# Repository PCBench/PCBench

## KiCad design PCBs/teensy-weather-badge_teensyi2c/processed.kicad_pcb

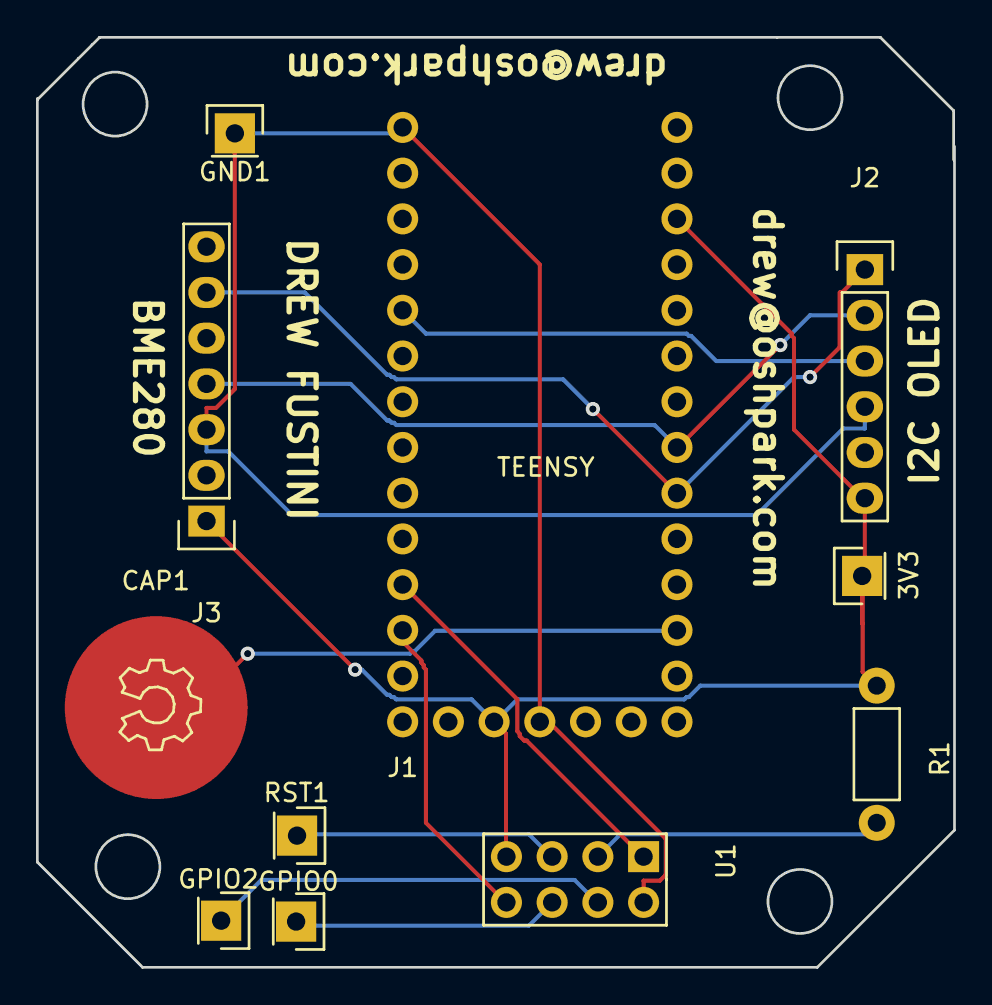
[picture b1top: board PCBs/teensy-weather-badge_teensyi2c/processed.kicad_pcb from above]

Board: 2 copper layers, 51.0 x 51.7 mm, 11 parts (0 on the bottom side), 12 nets.

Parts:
3V3: 3V3; Pin_Header_Straight_1x01
CAP1: CAPSENSE_CIRCLE; CAPSENSE_CIRCLE_D10
GND1: GND; Pin_Header_Straight_1x01
GPIO0: GPIO0; Pin_Header_Straight_1x01
GPIO2: GPIO2; Pin_Header_Straight_1x01
J1: TEENSY3.2-72MHz; TEENSY-LC
J2: OLED-I2C; Pin_Header_Straight_1x06
J3: ADAFRUIT_BME280; Pin_Header_Straight_1x07
R1: R; Resistor_Horizontal_RM7mm
RST1: RST; Pin_Header_Straight_1x01
U1: ESP-01v090; ESP-01

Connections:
/GND: GND1.1, J1.G1, J1.G2, J2.4, J3.3, U1.2
/RST: J1.3, J2.3
/SCK: J1.19, J2.2, J3.4
/SDA: J1.18, J2.1, J3.6
/VIN: 3V3.1, J1.3V1, J1.3V2, J2.6, J3.1, R1.1, U1.7
unnamed: CAP1.1, J1.15
unnamed: GPIO0.1, U1.6
unnamed: GPIO2.1, U1.4
unnamed: J1.9, U1.1
unnamed: J1.10, U1.8
unnamed: R1.2, U1.3
unnamed: RST1.1, U1.5

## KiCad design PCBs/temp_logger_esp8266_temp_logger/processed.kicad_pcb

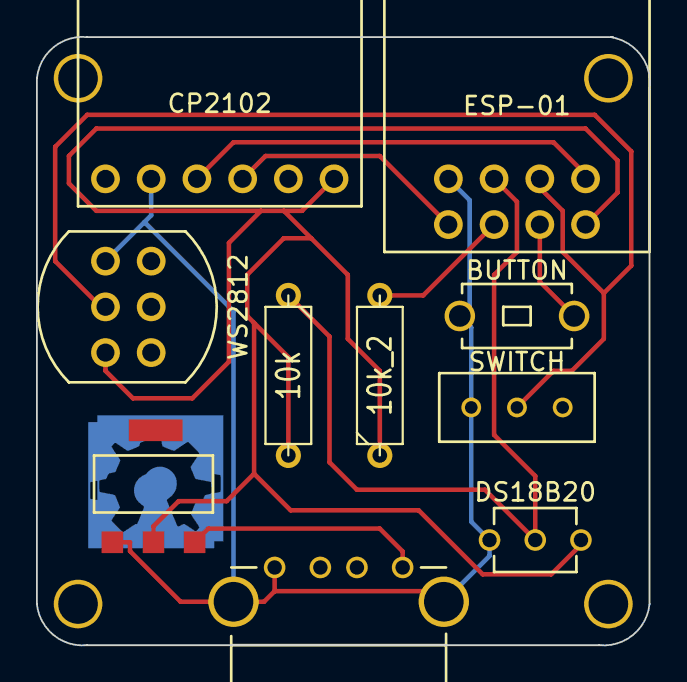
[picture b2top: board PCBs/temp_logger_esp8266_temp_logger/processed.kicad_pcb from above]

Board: 2 copper layers, 34.1 x 33.8 mm, 17 parts (0 on the bottom side), 9 nets.

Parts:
10k, 10k_2: R; R3-5
M2_1pin_custom, M2_1pin_custom_2, M2_1pin_custom_3, M2_1pin_custom_4: VAL**; M2_1pin_custom
SW1: SWITCH; switch_small_custom
SW2: BUTTON; button_single_custom
U1: CP2102; CP2102_Custom
U2: ESP-01; esp-01_custom
U3: WS2812; ws2812_custom
U4: DS18B20; ds18b20_custom
U5: 3.3_VOLTAGE_REG; AMS1117_custom
U6: MALE_USB_CUSTOM; male_usb_custom
VAL: OSH_final_silks_back
VAL_2, VAL_3: OSH_final

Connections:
unnamed: SW2.1, U2.6
unnamed: U5.3, U6.1
unnamed: SW1.2, U2.5, U3.2
unnamed: 10k.1, U2.3, U4.2
unnamed: SW1.1, SW2.2, U1.5, U2.1, U3.1, U4.1, U5.1, U6.4
unnamed: 10k_2.2, U2.4
unnamed: U1.4, U2.7
unnamed: 10k.2, 10k_2.1, U1.1, U2.8, U3.3, U4.3, U5.2
unnamed: U1.3, U2.2

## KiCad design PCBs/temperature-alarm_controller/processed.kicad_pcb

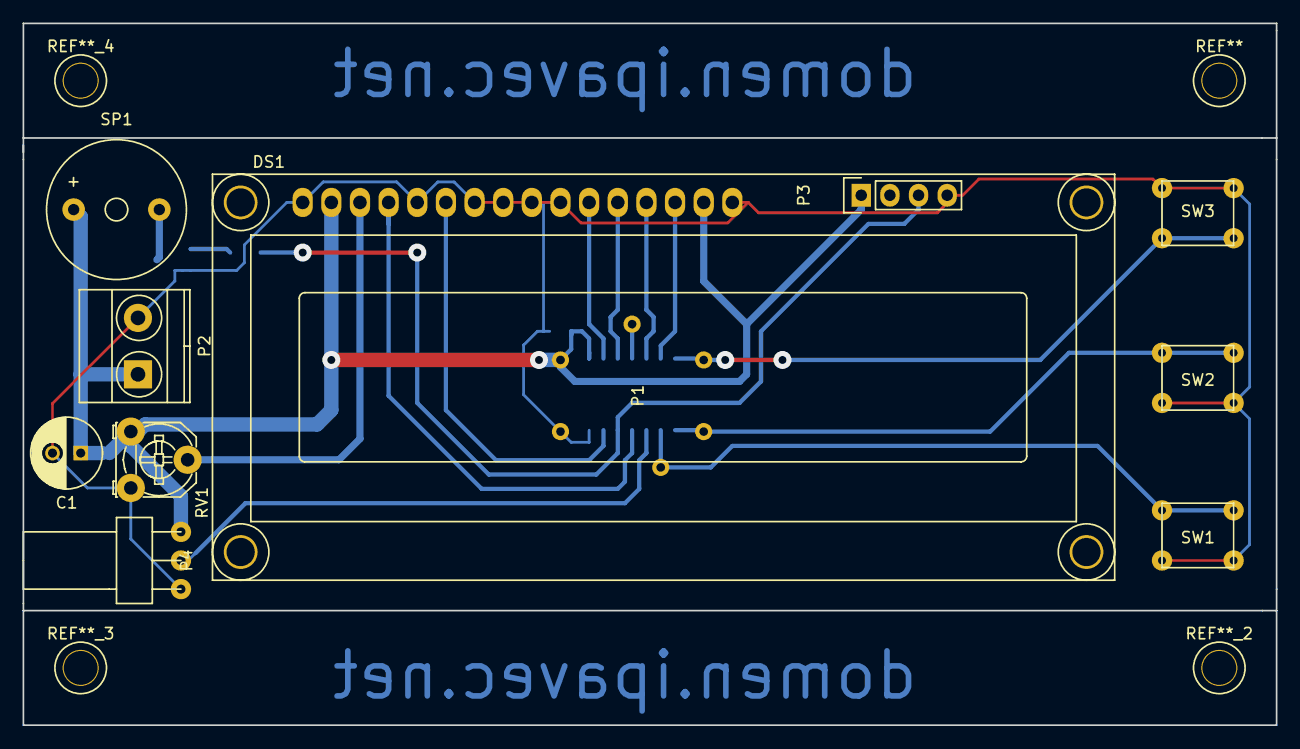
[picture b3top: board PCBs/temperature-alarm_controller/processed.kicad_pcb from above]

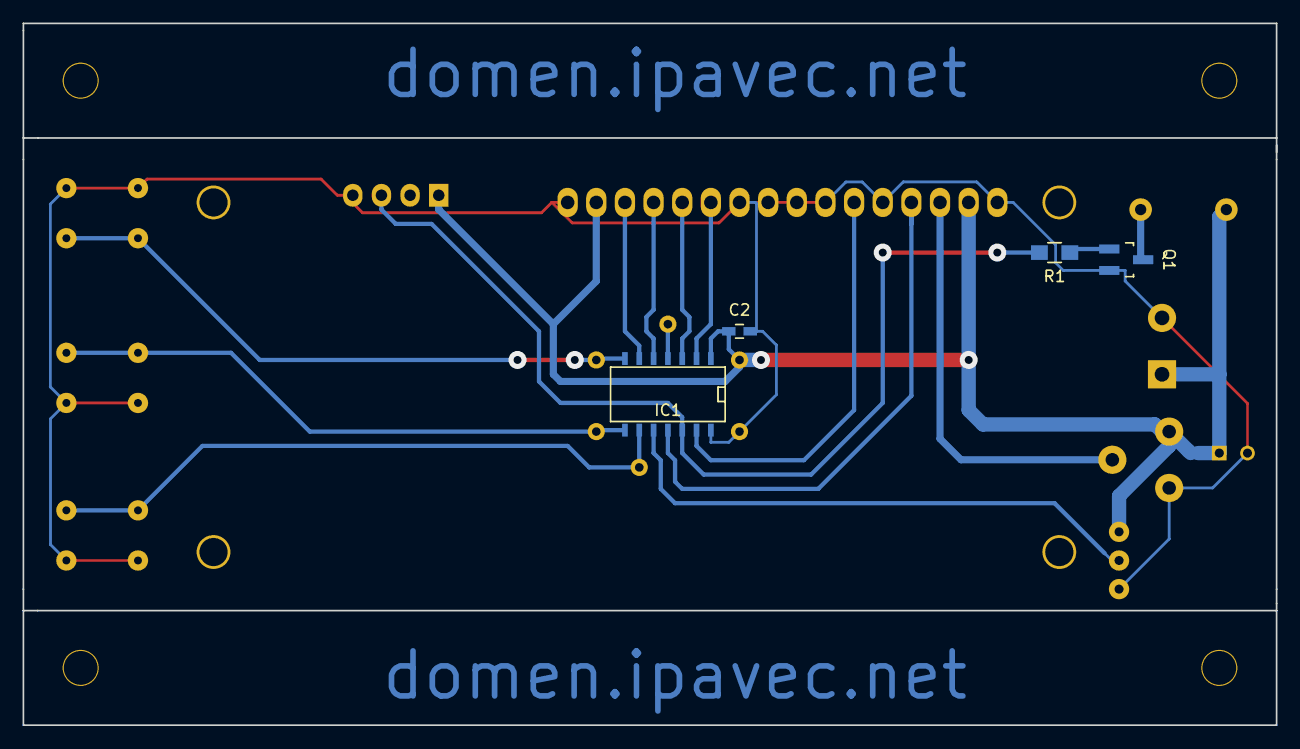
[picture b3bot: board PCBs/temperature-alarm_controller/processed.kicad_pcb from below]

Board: 2 copper layers, 111.1 x 62.2 mm, 15 parts (4 on the bottom side), 17 nets.

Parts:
C1: 100uF; C_Radial_D6.3_L11.2_P2.5
C2: 100nF; C_0603_HandSoldering
DS1: LCD16X2; WC1602A
IC1: ATTINY841-SSU; SOIC-14_N
P1: CONN_01X06; ATTINY841-SPI
P2: CONN_01X02; TerminalBlock_Pheonix_MKDS1.5-2pol
P3: CONN_01X04; Pin_Header_Straight_1x04
P4: CONN_01X03; fanconnector
Q1: Q_NPN_BEC; SOT-23_Handsoldering
R1: 4k7; R_0805_HandSoldering
RV1: POT; Potentiometer_Triwood_RM-065
SP1: SPEAKER; Buzzer_12x9.5RM7.6
SW1, SW2, SW3: SW_PUSH; pushbutton

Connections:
+5V: C1.1, C2.1, DS1.2, DS1.15, IC1.1, P1.2, P2.1, P3.1, P4.3, RV1.1, SP1.1
AVR_MISO: IC1.8, P1.1, SW2.2
AVR_MOSI: IC1.7, P1.4, SW3.2
AVR_RESET: IC1.4, P1.5
AVR_SCK: IC1.9, P1.3, SW1.2
D4: DS1.11, IC1.2
D5: DS1.12, IC1.3
D6: DS1.13, IC1.5
D7: DS1.14, IC1.6
DQ: IC1.10, P4.2
E: DS1.6, IC1.13
GND: C1.2, C2.2, DS1.1, DS1.5, DS1.7, DS1.8, DS1.9, DS1.10, DS1.16, IC1.14, P1.6, P2.2, P3.4, P4.1, Q1.2, RV1.3, SW1.1, SW2.1, SW3.1
unnamed: DS1.3, RV1.2
unnamed: Q1.1, R1.1
unnamed: Q1.3, SP1.2
RS: DS1.4, IC1.11
TXD: IC1.12, P3.3, R1.2

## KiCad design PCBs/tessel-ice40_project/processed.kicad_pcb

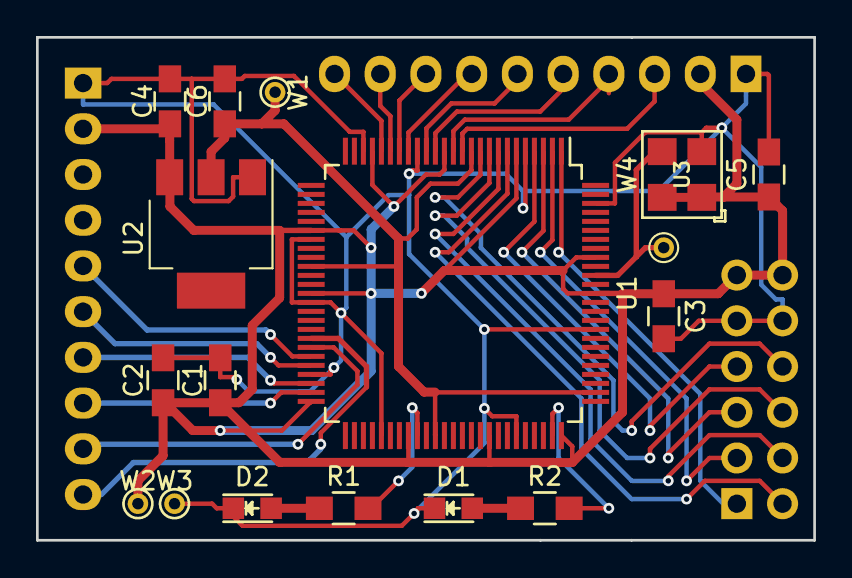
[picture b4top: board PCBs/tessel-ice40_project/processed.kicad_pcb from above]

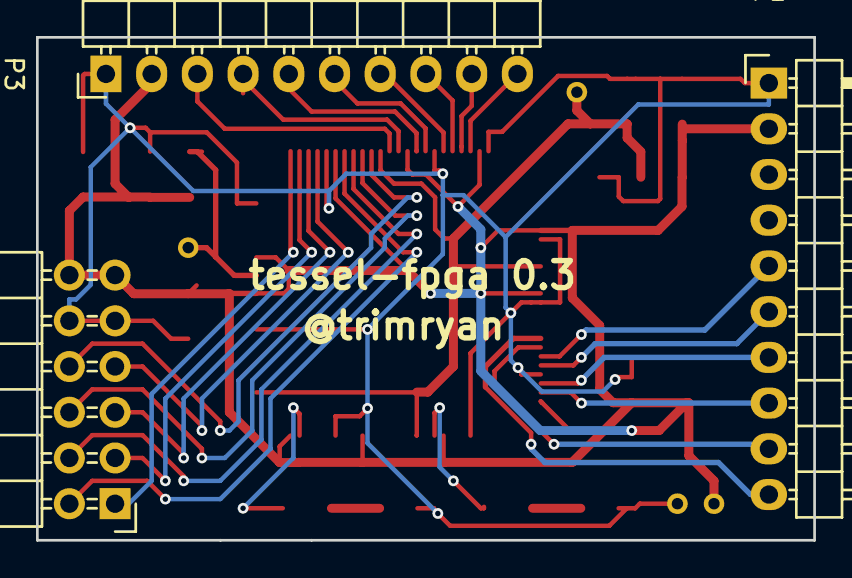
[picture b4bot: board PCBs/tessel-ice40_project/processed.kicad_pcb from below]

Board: 2 copper layers, 43.2 x 27.9 mm, 20 parts (3 on the bottom side), 30 nets.

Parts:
C1, C2, C3, C5: 0.1uF; C_0805_HandSoldering
C4: 100nF; C_0805_HandSoldering
C6: 10uF; C_0805_HandSoldering
D1, D2: LED; LED_0805
P1, P3: CONN_01X10; Pin_Header_Angled_1x10
P2: CONN_02X06; Pin_Header_Angled_2x06
R1, R2: 10K; R_0805_HandSoldering
U1: iCE40-HX1K-VQ100; LQFP-100_14x14mm_Pitch0.5mm
U2: LD1117S12CTR; SOT-223
U3: Si501-PKG-B; SILABS-DFN-SI501-B
W1, W4: TEST_1V2; PINTST
W2: TEST_3V3; PINTST
W3: TEST_GND; PINTST

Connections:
+1V2: C6.1, U1.11, U1.35, U1.61, U1.77, U2.2, W1.1
BANK_IO: C1.1, C2.1, C3.1, C4.1, C5.1, P1.2, P2.11, P2.12, P3.2, U1.6, U1.14, U1.22, U1.31, U1.38, U1.50, U1.58, U1.67, U1.75, U1.88, U1.92, U2.3, U3.1, U3.4, W2.1
CDONE: P1.10, U1.43
CRESET: P1.9, U1.44
GND: C1.2, C2.2, C3.2, C4.2, C5.2, C6.2, D1.1, D2.1, P1.1, P2.9, P2.10, P3.1, U1.5, U1.17, U1.23, U1.32, U1.39, U1.47, U1.55, U1.70, U1.84, U1.98, U2.1, U3.2, W3.1
LED1: R1.1, U1.59
LED2: R2.1, U1.74
MOD1: P3.3, U1.12
MOD2: P3.4, U1.13
MOD3: P3.5, U1.15
MOD4: P3.6, U1.16
MOD5: P3.7, U1.18
MOD6: P3.8, U1.19
MOD7: P3.9, U1.20
MOD8: P3.10, U1.21
unnamed: D1.2, R2.2
unnamed: D2.2, R1.2
unnamed: P1.5, U1.45
unnamed: P1.6, U1.46
unnamed: P1.7, U1.48
unnamed: P1.8, U1.49
unnamed: U1.90, U3.3, W4.1
PMOD1: P2.1, U1.1
PMOD2: P2.3, U1.2
PMOD3: P2.5, U1.3
PMOD4: P2.7, U1.4
PMOD7: P2.2, U1.7
PMOD8: P2.4, U1.8
PMOD9: P2.6, U1.9
PMOD10: P2.8, U1.10

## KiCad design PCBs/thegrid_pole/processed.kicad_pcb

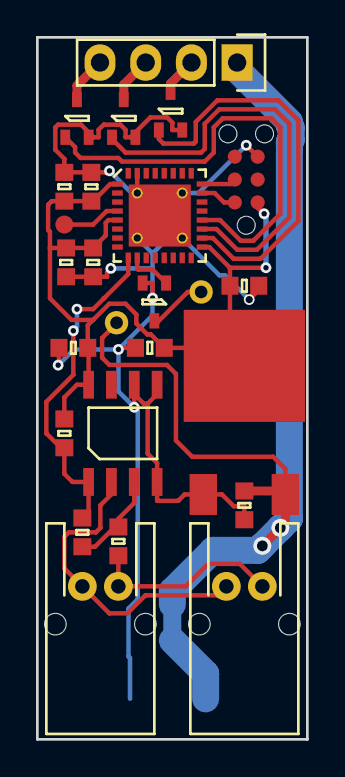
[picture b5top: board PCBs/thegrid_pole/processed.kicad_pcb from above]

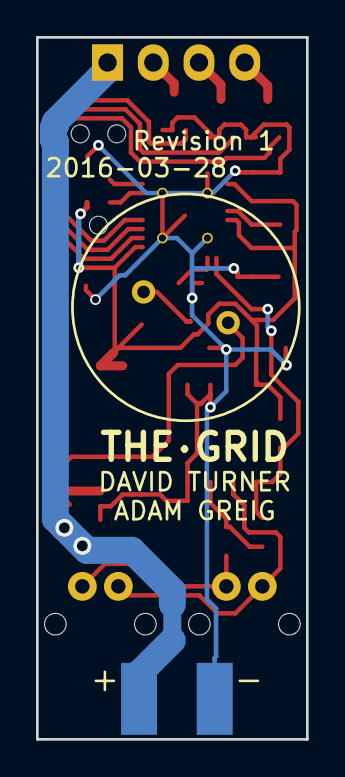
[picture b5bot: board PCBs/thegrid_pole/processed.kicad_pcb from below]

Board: 2 copper layers, 15.0 x 39.0 mm, 25 parts (2 on the bottom side), 18 nets.

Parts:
C1, C3, C5, C6: 100n; 0603
C2: 4u7; 0603
C4: 10n; 0603
C7: 10u; 0603
C8: 1u; 0603
IC1: LMx93; SOIC-8
IC2: STM32F0xxKxUx; QFN-32-EP-ST
P1: POWER_IN; minipow_edge
P2: BUS_IN; S02B-PASK-2
P3: BUS_OUT; S02B-PASK-2
P4: SWD_TC; TC2030-NL
P5: LEDs; Pin_Header_Straight_1x04
Q1, Q2, Q3, Q4: MTM232270LBF; SOT-323
R1, R2: 10k; 0603
R3: 1M; 0603
SP1: SPEAKER; piezo
TP1: RST; TESTPAD
U1: LD1117S33TR; TO-252-3

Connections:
+3V3: C1.2, C2.1, C3.1, C4.1, C5.1, C7.1, C8.1, IC1.8, IC2.1, IC2.5, IC2.17, P4.1, R1.1, U1.2
+12V: C6.1, P1.2, P5.1, SP1.1, U1.3
/BUS: IC1.1, IC2.9, R1.2, R3.1
/BUS_A: IC1.2, P2.1, P3.1
/BUS_B: P2.2, P3.2, R2.2
/DRIVE_B: P5.4, Q3.3
/DRIVE_G: P5.3, Q2.3
/DRIVE_R: P5.2, Q1.3
/LED_B: IC2.20, Q3.1
/LED_G: IC2.19, Q2.1
/LED_R: IC2.18, Q1.1
/PIEZO: IC2.10, Q4.1
/SWDCLK: IC2.24, P4.4
/SWDIO: IC2.23, P4.2
GND: C1.1, C2.2, C3.2, C4.2, C5.2, C6.2, C7.2, C8.2, IC1.4, IC1.5, IC1.6, IC2.31, IC2.EP, P1.1, P4.5, Q1.2, Q2.2, Q3.2, Q4.2, U1.1
unnamed: IC1.3, R2.1, R3.2
unnamed: IC2.4, TP1.1
unnamed: Q4.3, SP1.2
